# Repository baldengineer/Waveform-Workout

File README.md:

# Waveform-Workout

An open-source tool to test oscilloscopes for basic operation.

## Status

r1 is at the fab.

## Firmware

[Build and flash the trainer](firmware/README.md). The first boot starts both outputs with a 1 kHz sine at 1.00 Vpp centered on +0.75 V. Later boots restore the last selection from EEPROM. Use MODE and VALUE or the USB shell to select waveform, DC, XY and trigger exercises. An optional SSD1306 OLED on J6 shows the active mode and value.

## Design files

- [Schematic PDF](kicad/Waveform%20Workout%20Schematic.pdf)
- [PCB PDF](kicad/Waveform%20Workout%20PCB.pdf)
- [Open the project in KiCanvas](https://kicanvas.org/?repo=https%3A%2F%2Fgithub.com%2Fbaldengineer%2FWaveform-Workout%2Ftree%2Fmain%2Fkicad)

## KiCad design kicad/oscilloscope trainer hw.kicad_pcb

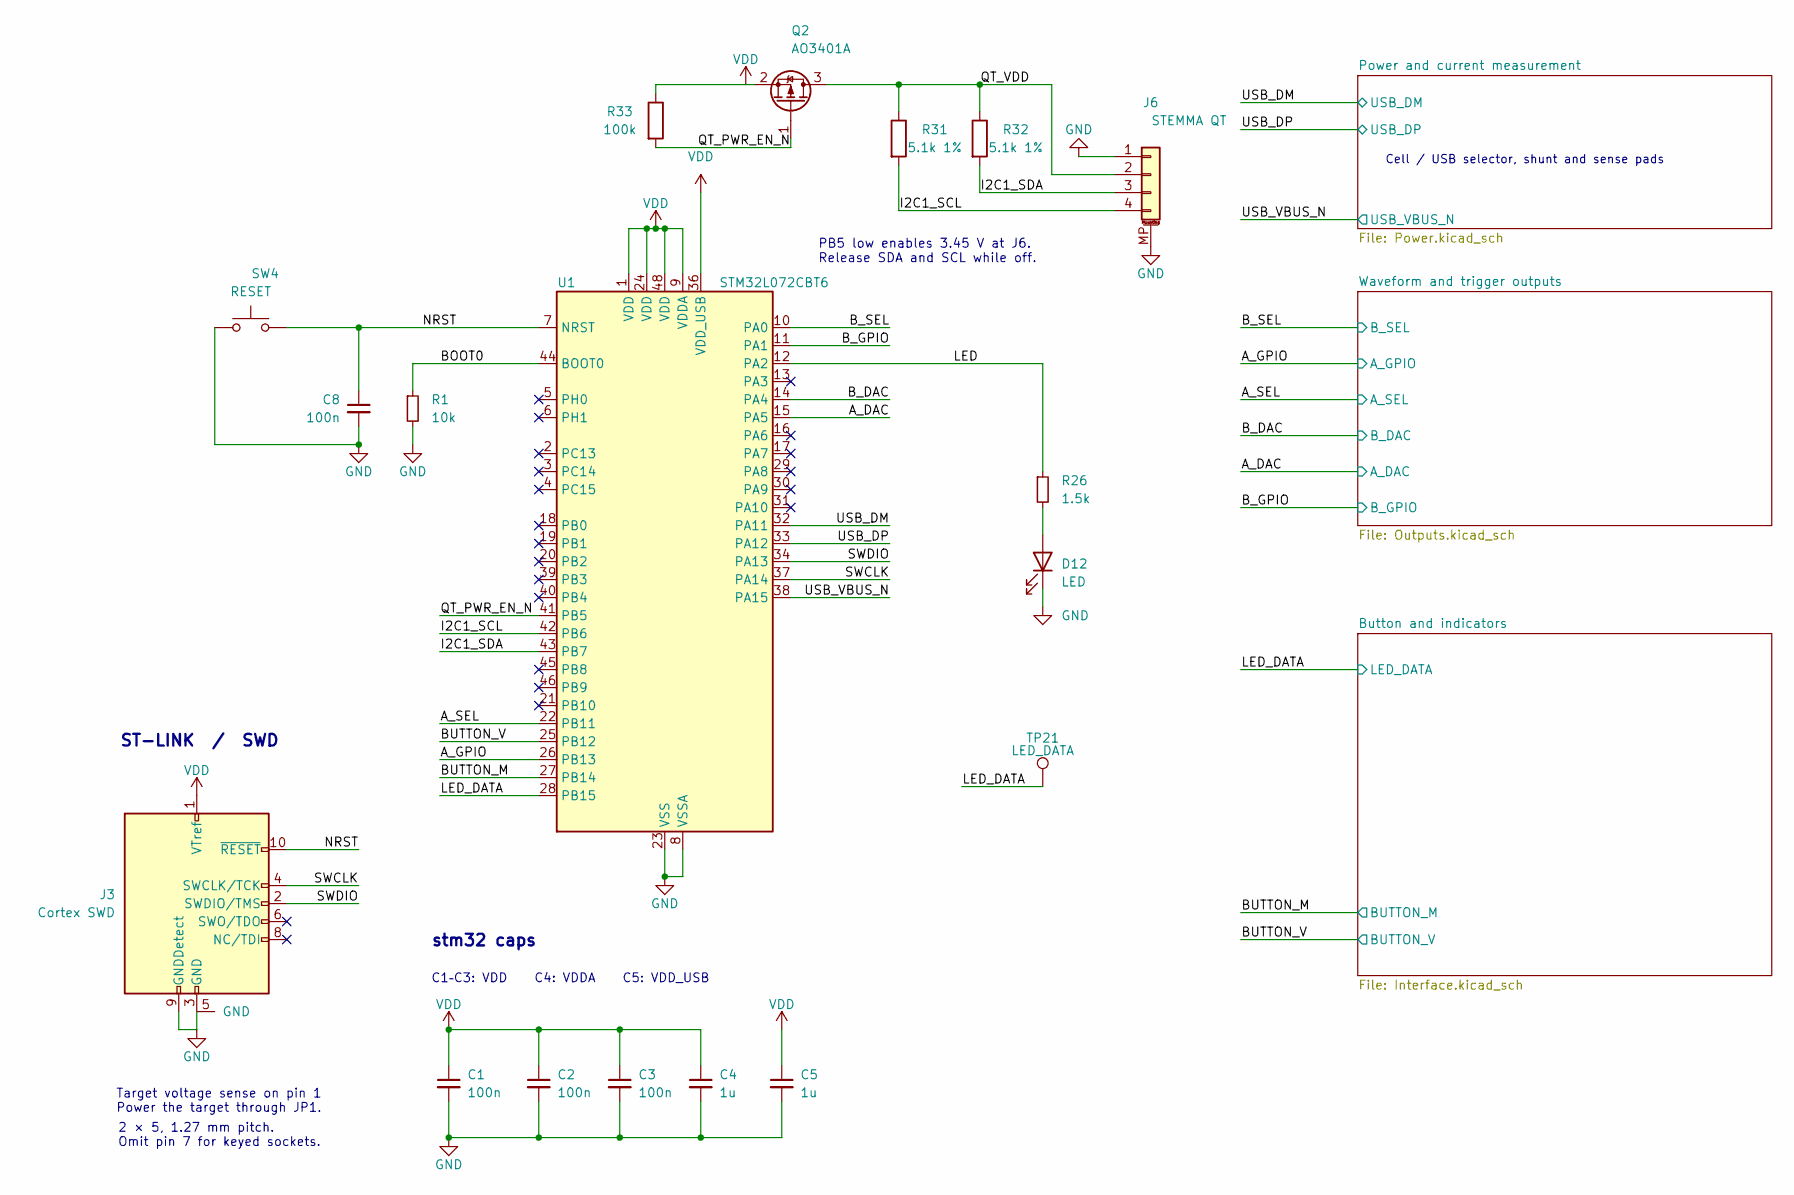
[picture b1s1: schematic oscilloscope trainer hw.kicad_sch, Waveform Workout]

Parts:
C1, C2, C3, C8: 100n; C_0603_1608Metric; MPN CC0603KRX7R9BB104; LCSC C14663
C4, C5: 1u; C_0603_1608Metric; MPN CC0603KRX5R9BB105; LCSC C128624
D12: LED; LED_0805_2012Metric; MPN KT-0805G; LCSC C2297
J3: Cortex SWD; Samtec_FTSH-105-01-L-DV-007-TR; MPN FTSH-105-01-L-DV-007-TR; LCSC C3347749
J6: STEMMA QT; JST_SH_SM04B-SRSS-TB_1x04-1MP_P1.00mm_Horizontal; MPN SM04B-SRSS-TB(LF)(SN); LCSC C160404
Q2: AO3401A; SOT-23; MPN AO3401A; LCSC C15127
R1: 10k; R_0603_1608Metric; MPN RC0603FR-0710KL; LCSC C98220
R26: 1.5k; R_0603_1608Metric; MPN 0603WAF1501T5E; LCSC C22843
R31, R32: 5.1k 1%; R_0603_1608Metric; MPN 0603WAF5101T5E; LCSC C23186
R33: 100k; R_0603_1608Metric; MPN 0603WAF1003T5E; LCSC C25803
SW4: RESET; SW_SPST_TS-1088-xR020; MPN TS-1088-AR02016; LCSC C720477
TP21: PB15; Harwin-S1751-46-Test-Point; MPN S1751-46; LCSC C3029083
U1: STM32L072CBT6; LQFP-48_7x7mm_P0.5mm; MPN STM32L072CBT6; LCSC C465977

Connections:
/A_DAC: U1.15 (PA5); also elsewhere on the board
/A_GPIO: U1.26 (PB13); also elsewhere on the board
/A_SEL: U1.22 (PB11); also elsewhere on the board
/BOOT0: R1.1, U1.44 (BOOT0)
/BUTTON_M: U1.27 (PB14); also elsewhere on the board
/BUTTON_V: U1.25 (PB12); also elsewhere on the board
/B_DAC: U1.14 (PA4); also elsewhere on the board
/B_GPIO: U1.11 (PA1); also elsewhere on the board
/B_SEL: U1.10 (PA0); also elsewhere on the board
/I2C1_SCL: J6.4, R31.2, U1.42 (PB6)
/I2C1_SDA: J6.3, R32.2, U1.43 (PB7)
/LED: R26.1, U1.12 (PA2)
/LED_DATA: TP21.1 (1_1), U1.28 (PB15); also elsewhere on the board
/NRST: C8.1, J3.10 (~RESET), SW4.2, U1.7 (NRST)
/QT_PWR_EN_N: Q2.1 (G), R33.2, U1.41 (PB5)
/QT_VDD: J6.2, Q2.3 (D), R31.1, R32.1
/SWCLK: J3.4 (SWCLK/TCK), U1.37 (PA14)
/SWDIO: J3.2 (SWDIO/TMS), U1.34 (PA13)
/USB_DM: U1.32 (PA11); also elsewhere on the board
/USB_DP: U1.33 (PA12); also elsewhere on the board
/USB_VBUS_N: U1.38 (PA15); also elsewhere on the board
unnamed: D12.2 (A), R26.2
VDD: C1.1, C2.1, C3.1, C4.1, C5.1, J3.1 (VTref), Q2.2 (S), R33.1, U1.1 (VDD), U1.9 (VDDA), U1.24 (VDD), U1.36 (VDD_USB), U1.48 (VDD); also elsewhere on the board

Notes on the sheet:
C1–C3: VDD C4: VDDA C5: VDD_USB
Target voltage sense on pin 1 Power the target through JP1.
PB5 low enables 3.45 V at J6. Release SDA and SCL while off.
ST-LINK / SWD
Cell / USB selector, shunt and sense pads
stm32 caps
2 × 5, 1.27 mm pitch. Omit pin 7 for keyed sockets.

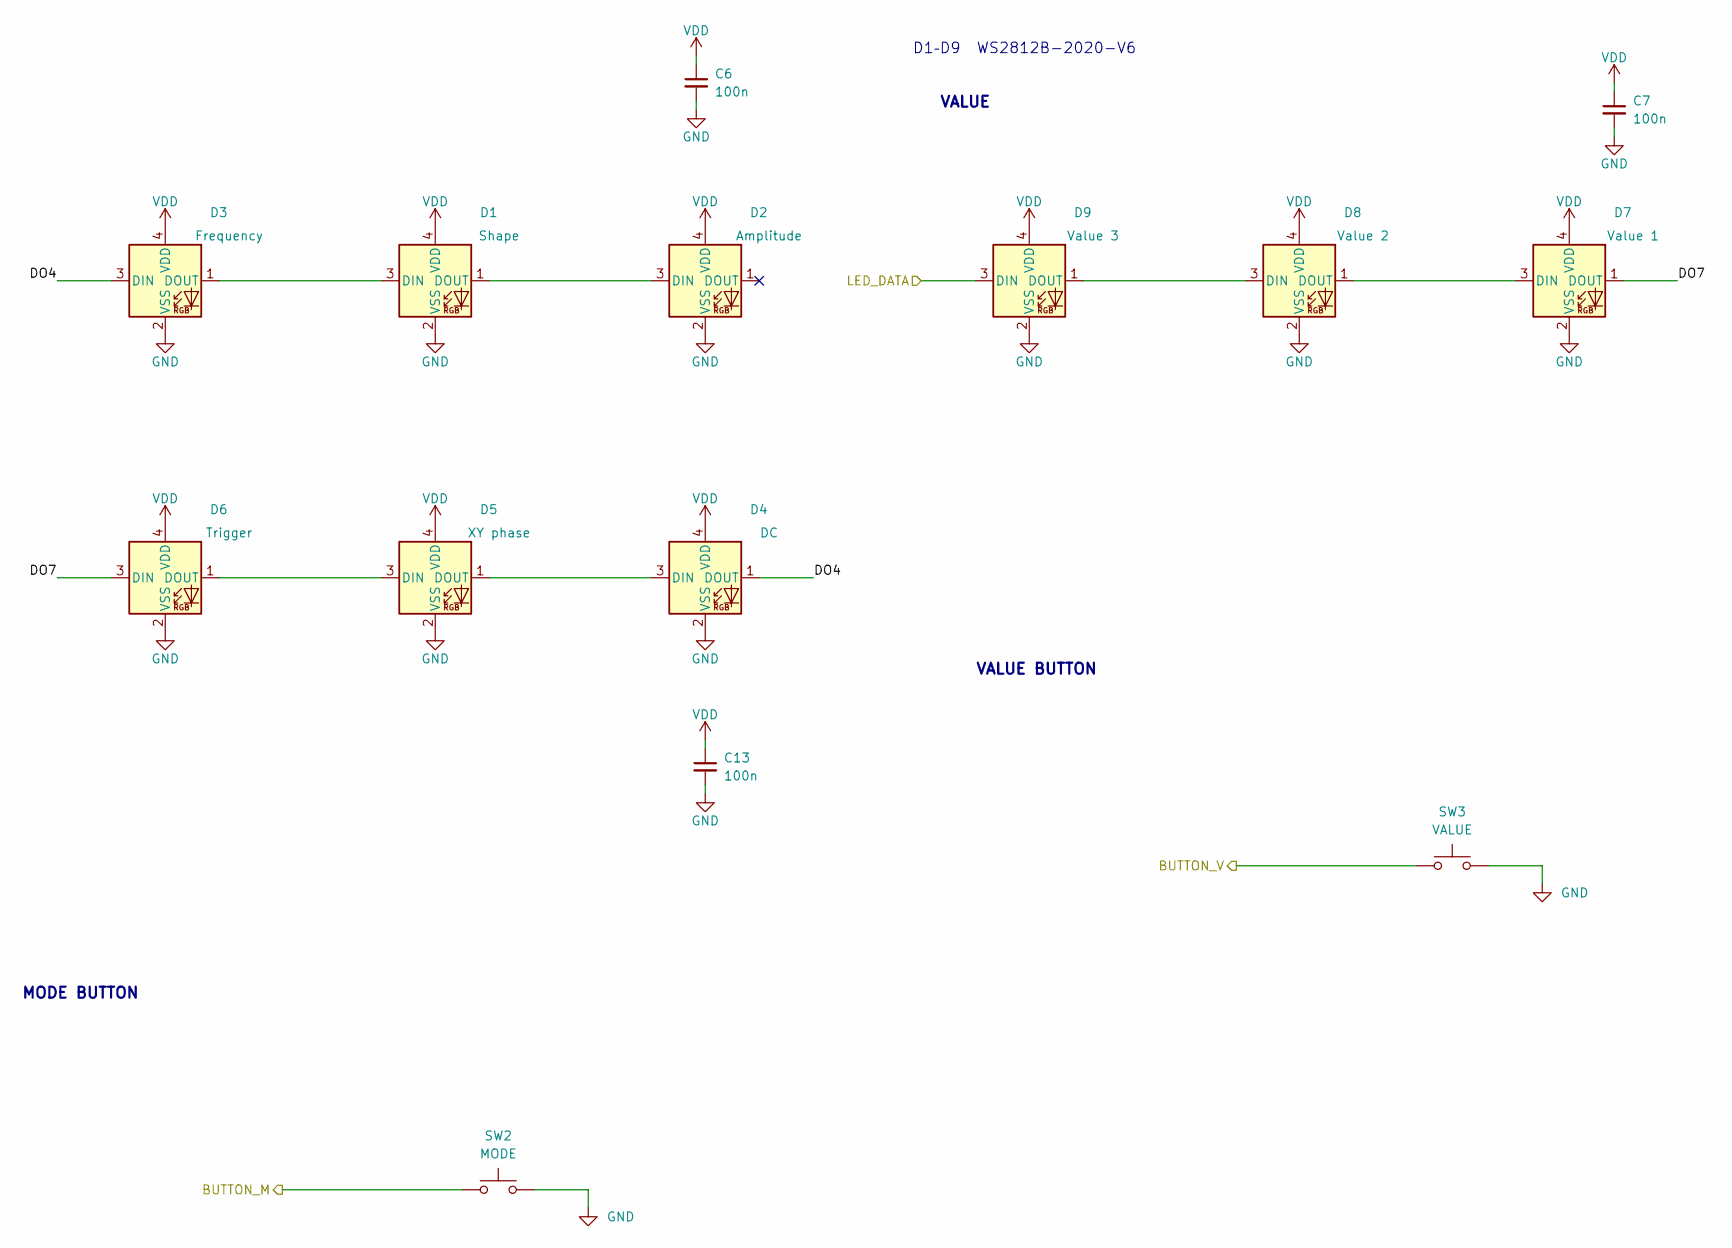
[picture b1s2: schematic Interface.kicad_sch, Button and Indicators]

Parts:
C6, C7, C13: 100n; C_0603_1608Metric; MPN CC0603KRX7R9BB104; LCSC C14663
D1, D2, D3, D4, D5, D6, D7, D8, D9: WS2812B-2020-V6; LED_WS2812B-2020_PLCC4_2.0x2.0mm; MPN WS2812B-2020-V6; LCSC C52917434
SW2: MODE; SW_SPST_TS-1088-xR020; MPN TS-1088-AR02016; LCSC C720477
SW3: VALUE; SW_SPST_TS-1088-xR020; MPN TS-1088-AR02016; LCSC C720477

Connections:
/BUTTON_M: SW2.1; also elsewhere on the board
/BUTTON_V: SW3.1; also elsewhere on the board
/Button and indicators/DO4: D3.3 (DIN), D4.1 (DOUT)
/Button and indicators/DO7: D6.3 (DIN), D7.1 (DOUT)
/LED_DATA: D9.3 (DIN); also elsewhere on the board
unnamed: D1.3 (DIN), D3.1 (DOUT)
unnamed: D1.1 (DOUT), D2.3 (DIN)
unnamed: D4.3 (DIN), D5.1 (DOUT)
unnamed: D5.3 (DIN), D6.1 (DOUT)
unnamed: D7.3 (DIN), D8.1 (DOUT)
unnamed: D8.3 (DIN), D9.1 (DOUT)
VDD: C6.1, C7.1, C13.1, D1.4 (VDD), D2.4 (VDD), D3.4 (VDD), D4.4 (VDD), D5.4 (VDD), D6.4 (VDD), D7.4 (VDD), D8.4 (VDD), D9.4 (VDD); also elsewhere on the board

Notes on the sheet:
VALUE
MODE BUTTON
VALUE BUTTON
D1–D9 WS2812B-2020-V6

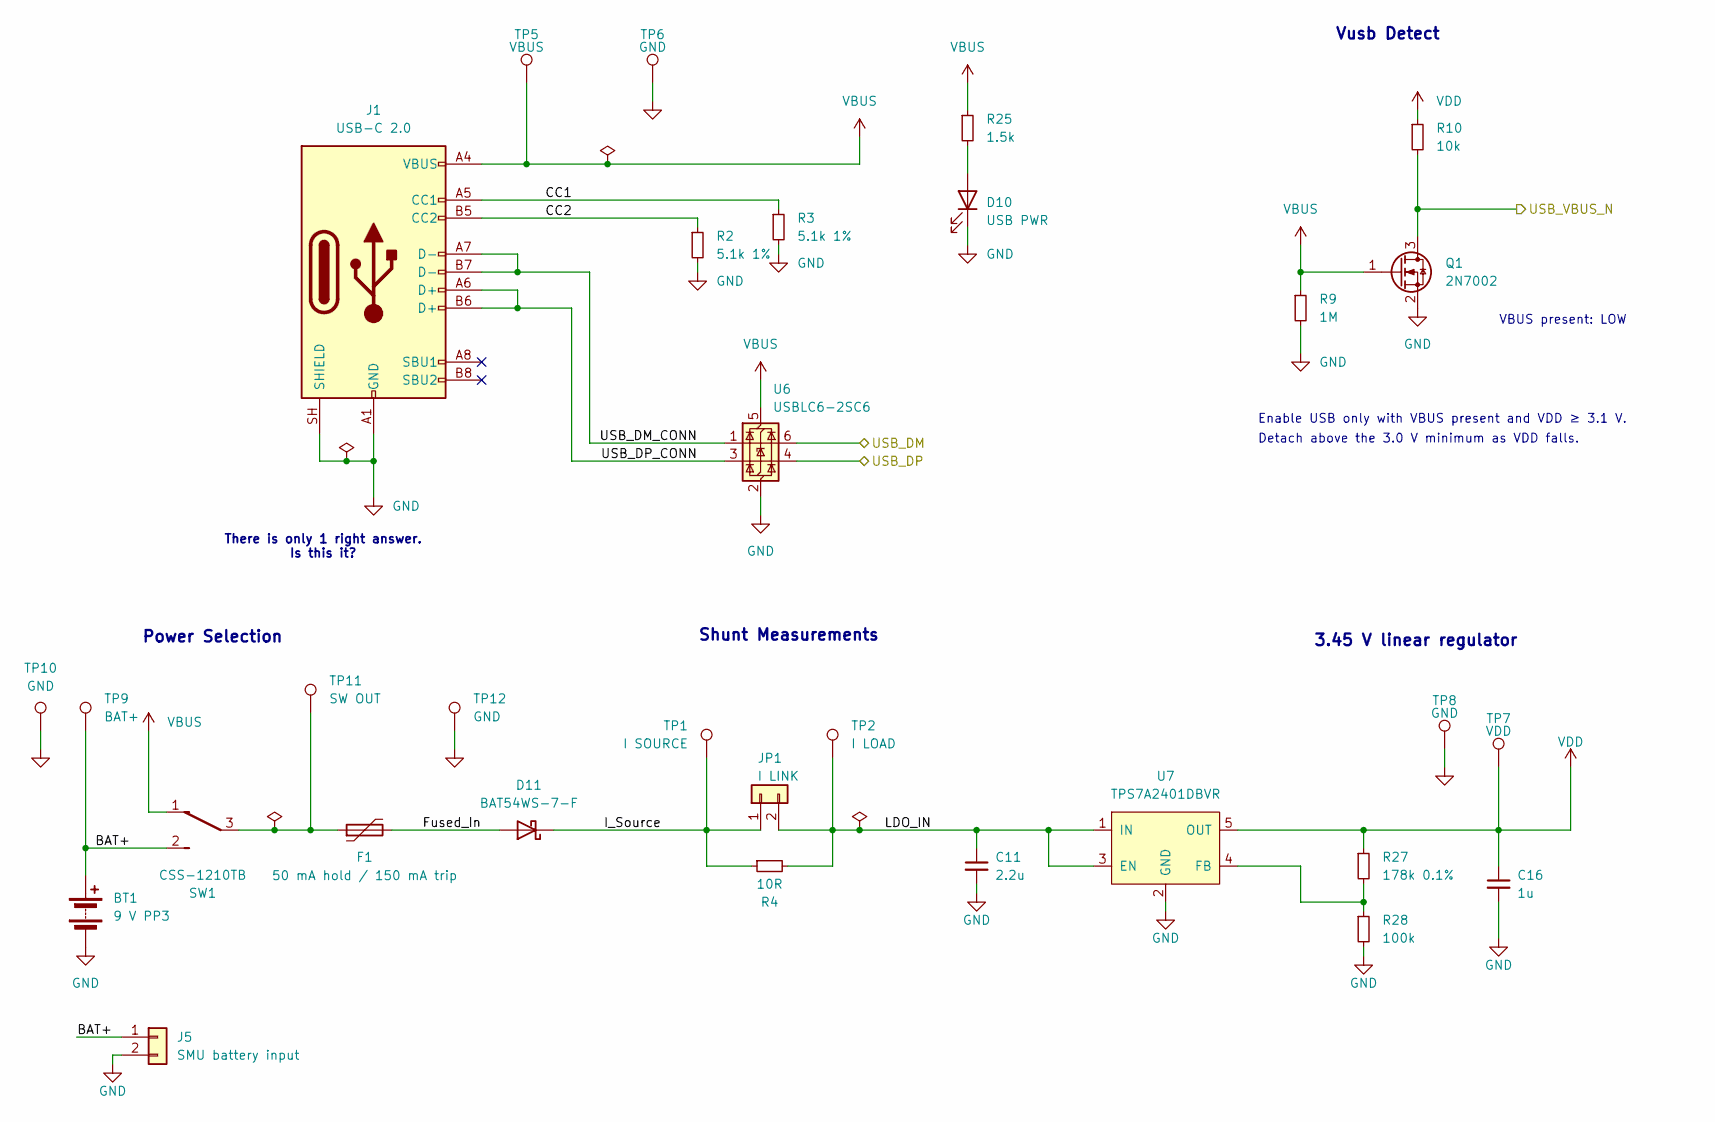
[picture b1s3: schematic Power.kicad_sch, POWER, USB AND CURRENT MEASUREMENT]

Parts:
BT1: 9 V PP3; BatteryHolder_Keystone_1290-79_1xPP3_Adhesive_Wire; MPN 1290-79
C11: 2.2u; C_0603_1608Metric; MPN CL10A225KO8NNNC; LCSC C23630
C16: 1u; C_0603_1608Metric; MPN CC0603KRX5R9BB105; LCSC C128624
D10: USB PWR; LED_0805_2012Metric; MPN KT-0805G; LCSC C2297
D11: BAT54WS-7-F; D_SOD-323; MPN BAT54WS-7-F; LCSC C124205
F1: 50 mA hold / 150 mA trip; Fuse_1206_3216Metric; MPN 1206L005/60WR; LCSC C315892
J1: USB-C 2.0; USB_C_Receptacle_GCT_USB4105-xx-A_16P_TopMnt_Horizontal; MPN USB4105-GF-A; LCSC C3020560
J5: SMU battery input; PinHeader_1x02_P2.54mm_Vertical; MPN PZ254V-11-02P; LCSC C492401
JP1: I LINK; PinHeader_1x02_P2.54mm_Vertical; MPN PZ254V-11-02P; LCSC C492401
Q1: 2N7002; SOT-23; MPN 2N7002; LCSC C8545
R2, R3: 5.1k 1%; R_0603_1608Metric; MPN 0603WAF5101T5E; LCSC C23186
R4: 10R; R_0805_2012Metric; MPN 0805W8F100JT5E; LCSC C17415
R9: 1M; R_0603_1608Metric; MPN 0603WAF1004T5E; LCSC C22935
R10: 10k; R_0603_1608Metric; MPN RC0603FR-0710KL; LCSC C98220
R25: 1.5k; R_0603_1608Metric; MPN 0603WAF1501T5E; LCSC C22843
R27: 178k 0.1%; R_0603_1608Metric; MPN ARG03BTC1783; LCSC C2441185
R28: 100k; R_0603_1608Metric; MPN 0603WAF1003T5E; LCSC C25803
SW1: CSS-1210TB; SW_SPDT_Nidec_CSS-1210TB; MPN CSS-1210TB; LCSC C2921710
TP1: I SOURCE; Harwin-S1751-46-Test-Point; MPN S1751-46; LCSC C3029083
TP2: I LOAD; Harwin-S1751-46-Test-Point; MPN S1751-46; LCSC C3029083
TP5: VBUS; Harwin-S1751-46-Test-Point; MPN S1751-46; LCSC C3029083
TP6, TP8, TP10, TP12: GND; Harwin-S1751-46-Test-Point; MPN S1751-46; LCSC C3029083
TP7: VDD; Harwin-S1751-46-Test-Point; MPN S1751-46; LCSC C3029083
TP9: BAT+; Harwin-S1751-46-Test-Point; MPN S1751-46; LCSC C3029083
TP11: SW OUT; Harwin-S1751-46-Test-Point; MPN S1751-46; LCSC C3029083
U6: USBLC6-2SC6; SOT-23-6; MPN USBLC6-2SC6; LCSC C7519
U7: TPS7A2401DBVR; SOT-23-5; MPN TPS7A2401DBVR; LCSC C2693328

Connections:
/Power and current measurement/BAT+: BT1.1 (+), J5.1, SW1.2 (B), TP9.1 (1_1)
/Power and current measurement/CC1: J1.A5 (CC1), R3.1
/Power and current measurement/CC2: J1.B5 (CC2), R2.1
/Power and current measurement/Fused_In: D11.2 (A), F1.2
/Power and current measurement/I_Source: D11.1 (K), JP1.1, R4.1, TP1.1 (1_1)
/Power and current measurement/USB_DM_CONN: J1.A7 (D-), J1.B7 (D-), U6.1 (I/O1)
/Power and current measurement/USB_DP_CONN: J1.A6 (D+), J1.B6 (D+), U6.3 (I/O2)
/USB_DM: U6.6 (I/O1); also elsewhere on the board
/USB_DP: U6.4 (I/O2); also elsewhere on the board
/USB_VBUS_N: Q1.3 (D), R10.2; also elsewhere on the board
unnamed: D10.2 (A), R25.2
unnamed: R27.2, R28.1, U7.4 (FB)
VDD: C16.1, R10.1, R27.1, TP7.1 (1_1), U7.5 (OUT); also elsewhere on the board

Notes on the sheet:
Shunt Measurements
3.45 V linear regulator
Vusb Detect
Enable USB only with VBUS present and VDD ≥ 3.1 V.
Power Selection
VBUS present: LOW
There is only 1 right answer. Is this it?
Detach above the 3.0 V minimum as VDD falls.

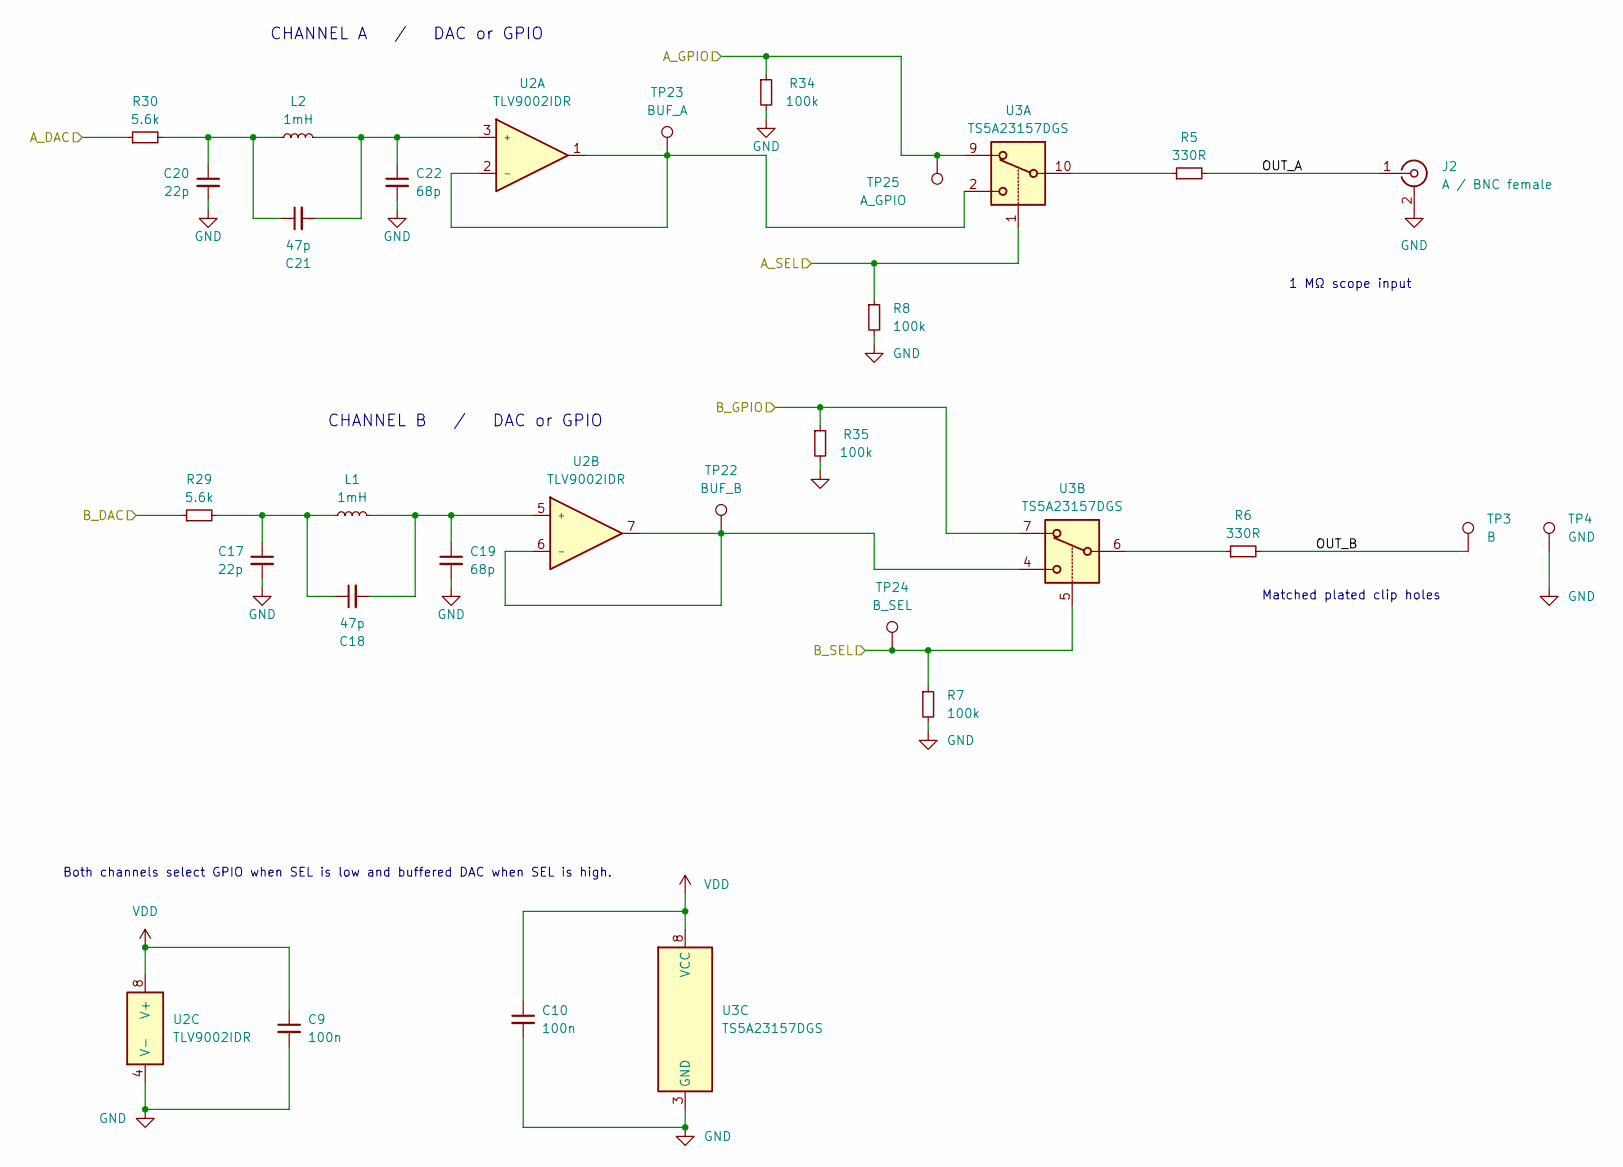
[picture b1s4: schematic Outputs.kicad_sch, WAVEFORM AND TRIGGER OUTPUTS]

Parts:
C9, C10: 100n; C_0603_1608Metric; MPN CC0603KRX7R9BB104; LCSC C14663
C17, C20: 22p; C_0805_2012Metric_Pad1.18x1.45mm_HandSolder; MPN CL21C220JBANNNC; LCSC C1804
C18, C21: 47p; C_0805_2012Metric_Pad1.18x1.45mm_HandSolder; MPN CL21C470JBANNNC; LCSC C14857
C19, C22: 68p; C_0805_2012Metric_Pad1.18x1.45mm_HandSolder; MPN 0805CG680J500NT; LCSC C1834
J2: A / BNC female; BNC_Kinghelm_KH-BNC50-3511_Horizontal; MPN KH-BNC50-3511; LCSC C2837587
L1, L2: 1mH; L_1812_4532Metric_Pad1.30x3.40mm_HandSolder; MPN 1812LS-105XJRC
R5, R6: 330R; R_0603_1608Metric; MPN 0603WAF3300T5E; LCSC C23138
R7, R8, R34, R35: 100k; R_0603_1608Metric; MPN 0603WAF1003T5E; LCSC C25803
R29, R30: 5.6k; R_0805_2012Metric_Pad1.20x1.40mm_HandSolder; MPN 0805W8F5601T5E; LCSC C4382
TP3: B; TestPoint_Plated_Hole_D3.0mm
TP4: GND; Harwin-S1751-46-Test-Point; MPN S1751-46; LCSC C3029083
TP22: BUF_B; Harwin-S1751-46-Test-Point; MPN S1751-46; LCSC C3029083
TP23: BUF_A; Harwin-S1751-46-Test-Point; MPN S1751-46; LCSC C3029083
TP24: B_SEL; Harwin-S1751-46-Test-Point; MPN S1751-46; LCSC C3029083
TP25: A_GPIO; Harwin-S1751-46-Test-Point; MPN S1751-46; LCSC C3029083
U2: TLV9002IDR; SOIC-8_3.9x4.9mm_P1.27mm; MPN TLV9002IDR; LCSC C398360
U3: TS5A23157DGS; TSSOP-10_3x3mm_P0.5mm; MPN TS5A23157DGSR; LCSC C11133

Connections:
/A_DAC: R30.1; also elsewhere on the board
/A_GPIO: R34.1, TP25.1 (1_1), U3.9; also elsewhere on the board
/A_SEL: R8.1, U3.1; also elsewhere on the board
/B_DAC: R29.1; also elsewhere on the board
/B_GPIO: R35.1, U3.7; also elsewhere on the board
/B_SEL: R7.1, TP24.1 (1_1), U3.5; also elsewhere on the board
/Waveform and trigger outputs/OUT_A: J2.1 (In), R5.2
/Waveform and trigger outputs/OUT_B: R6.2, TP3.1 (1_1)
unnamed: C17.1, C18.1, L1.1, R29.2
unnamed: C20.1, C21.1, L2.1, R30.2
unnamed: R5.1, U3.10
unnamed: R6.1, U3.6
unnamed: C21.2, C22.1, L2.2, U2.3 (+)
unnamed: TP23.1 (1_1), U2.1, U2.2 (−), U3.2
unnamed: C18.2, C19.1, L1.2, U2.5 (+)
unnamed: TP22.1 (1_1), U2.6 (−), U2.7, U3.4
VDD: C9.1, C10.1, U2.8 (V+), U3.8 (VCC); also elsewhere on the board

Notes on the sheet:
Matched plated clip holes
Both channels select GPIO when SEL is low and buffered DAC when SEL is high.
CHANNEL B / DAC or GPIO
1 MΩ scope input
CHANNEL A / DAC or GPIO

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
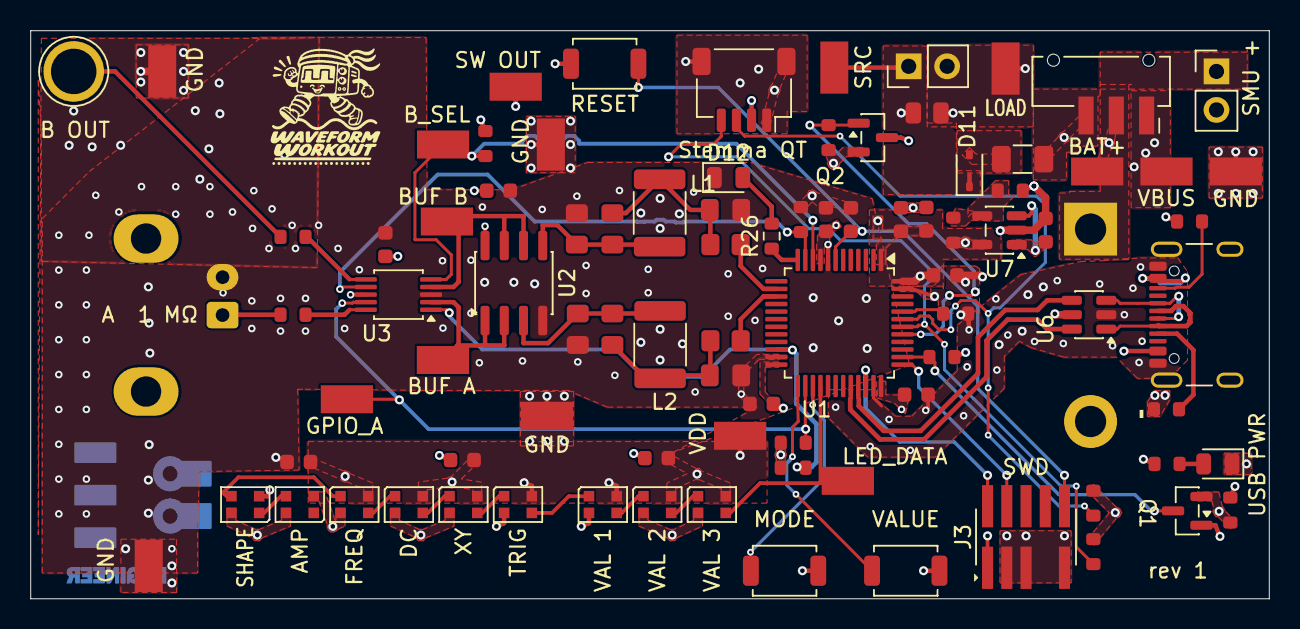
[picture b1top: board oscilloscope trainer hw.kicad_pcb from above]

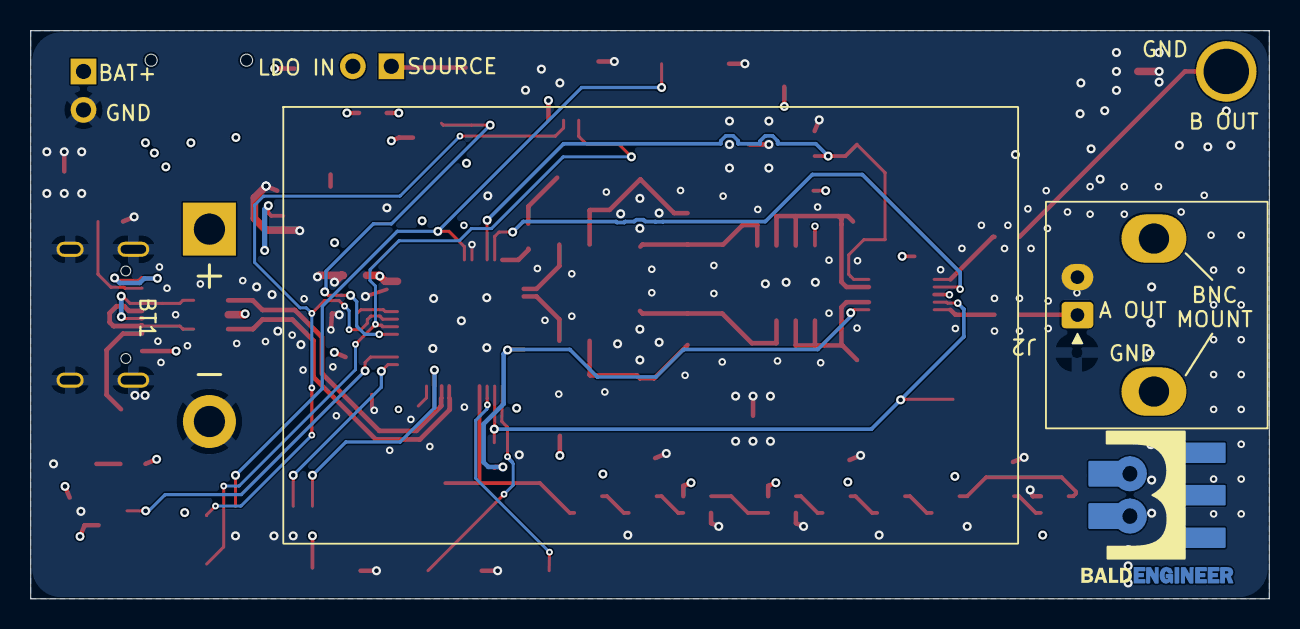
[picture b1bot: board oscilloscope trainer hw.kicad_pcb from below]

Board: 4 copper layers, 81.8 x 37.5 mm, 91 parts (3 on the bottom side), 54 nets.

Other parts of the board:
svg2mod: G***; BE10v2

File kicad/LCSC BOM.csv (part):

References,Fit qty per trainer,Part / schematic value,Manufacturer,MPN,LCSC,Ready to ship at check,Checked UTC,LCSC product page,Assembly / sourcing status,Footprint,Notes,Datasheet
BT1,1,9 V PP3,Keystone Electronics,1290-79,,,,,External sourcing,Trainer:BatteryHolder_Keystone_1290-79_1xPP3_Adhesive_Wire,Glue the holder to the back with electrically insulating adhesive. Wire the positive lug to pad 1 (BAT+) and the negative lug to pad 2 (GND). Remove the PP3 before applying an external battery-emulation voltage to J5.,https://media.soselectronic.com/KatList/keystone/1290-79.pdf
BT1 battery,1,9 V alkaline PP3,,,,,,,User supplied,,Remove the battery when using J5 for SMU emulation.,
"C1, C2, C3, C6, C7, C8, C9, C10, C13",9,100n,YAGEO,CC0603KRX7R9BB104,C14663,908800,2026-11-23T04:45:07Z,https://www.lcsc.com/product-detail/C14663.html,Populate,Capacitor_SMD:C_0603_1608Metric,,https://datasheet.lcsc.com/datasheet/pdf/23ccee80ee542e7cf15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
"C4, C5, C16",3,1u,YAGEO,CC0603KRX5R9BB105,C128624,135600,2026-11-23T04:45:06Z,https://www.lcsc.com/product-detail/C128624.html,Populate,Capacitor_SMD:C_0603_1608Metric,"1 µF, 50 V, X5R, ±10%.",https://datasheet.lcsc.com/datasheet/pdf/5b3aae1e7925073bc9b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
C11,1,2.2u,Samsung Electro-Mechanics,CL10A225KO8NNNC,C23630,288150,2026-11-23T04:45:09Z,https://www.lcsc.com/product-detail/C23630.html,Populate,Capacitor_SMD:C_0603_1608Metric,,https://datasheet.lcsc.com/datasheet/pdf/02336ea48ea44ca18c7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
"C17, C20",2,22p,Samsung Electro-Mechanics,CL21C220JBANNNC,C1804,132200,2026-11-23T04:45:08Z,https://www.lcsc.com/product-detail/C1804.html,Populate,Capacitor_SMD:C_0805_2012Metric_Pad1.18x1.45mm_HandSolder,"DAC filter, 0805 C0G, 50 V, ±5%.",https://datasheet.lcsc.com/datasheet/pdf/02336ea48ea44ca18c7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
"C18, C21",2,47p,Samsung Electro-Mechanics,CL21C470JBANNNC,C14857,82360,2026-11-23T04:45:07Z,https://www.lcsc.com/product-detail/C14857.html,Populate,Capacitor_SMD:C_0805_2012Metric_Pad1.18x1.45mm_HandSolder,"DAC filter tank capacitors, 0805 C0G, 50 V, ±5%.",https://datasheet.lcsc.com/datasheet/pdf/02336ea48ea44ca18c7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
"C19, C22",2,68p,FH,0805CG680J500NT,C1834,28200,2026-11-23T04:45:08Z,https://www.lcsc.com/product-detail/C1834.html,Populate,Capacitor_SMD:C_0805_2012Metric_Pad1.18x1.45mm_HandSolder,"DAC filter, 0805 C0G, 50 V, ±5%.",https://datasheet.lcsc.com/datasheet/pdf/09fe2daf22580a99fa7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
"D1, D2, D3, D4, D5, D6, D7, D8, D9",9,WS2812B-2020-V6,Worldsemi,WS2812B-2020-V6,C52917434,688000,2026-11-23T04:45:12Z,https://www.lcsc.com/product-detail/C52917434.html,Populate,Trainer:LED_WS2812B-2020_PLCC4_2.0x2.0mm,"Six mode and three value indicators. Data from PB15 passes through D9, D8, D7, D6, D5, D4, D3, D1, then D2. Limit brightness and simultaneous channel current in firmware.",https://www.world-semi.com/downloads/datasheets/en/ws2812b-2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
D10,1,"USB power indicator, green 0805",Hubei KENTO Electronics,KT-0805G,C2297,2056300,2026-11-23T04:45:09Z,https://www.lcsc.com/product-detail/C2297.html,Populate,LED_SMD:LED_0805_2012Metric,Independent USB power indication with R25.,https://datasheet.lcsc.com/datasheet/pdf/de342fde3322df07970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
D11,1,BAT54WS-7-F,Diodes Incorporated,BAT54WS-7-F,C124205,79715,2026-11-23T04:45:06Z,https://www.lcsc.com/product-detail/C124205.html,Populate,Diode_SMD:D_SOD-323,Anode (pad 2) connects to F1. Cathode (pad 1) feeds the source side of JP1 and R4 at TP1.,https://www.diodes.com/datasheet/download/BAT54WS.pdf
F1,1,50 mA hold / 150 mA trip,Littelfuse,1206L005/60WR,C315892,,,https://www.lcsc.com/product-detail/C315892.html,Populate,Fuse:Fuse_1206_3216Metric,"60 V surface-mount resettable PPTC for the trainer and accessory supply. Maximum time to trip is 1.5 s at 250 mA.",https://www.littelfuse.com/assetdocs/littelfuse-ptc-1206l-da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
J1,1,USB-C 2.0,GCT,USB4105-GF-A,C3020560,749,2026-11-23T04:45:11Z,https://www.lcsc.com/product-detail/C3020560.html,Populate,Connector_USB:USB_C_Receptacle_GCT_USB4105-xx-A_16P_TopMnt_Horizontal,,https://gct.co/files/drawings/usb4105.pdf
J2,1,A / BNC female,Kinghelm,KH-BNC50-3511,C2837587,9313,2026-11-23T04:45:10Z,https://www.lcsc.com/product-detail/C2837587.html,Populate,Trainer:BNC_Kinghelm_KH-BNC50-3511_Horizontal,50 ohm right-angle through-hole jack with panel nut and washer. Use a male-to-male BNC coupler with the scope's 1 megohm input.,https://www.kinghelm.com.cn/upload/file/20221214/KH-BNC50-3511.pdf
J3,1,Cortex SWD,Samtec,FTSH-105-01-L-DV-007-TR,C3347749,,,https://www.lcsc.com/product-detail/C3347749.html,Populate,Trainer:Samtec_FTSH-105-01-L-DV-007-TR,"Vertical 1.27 mm SMT Cortex debug header, position 7 omitted.",https://suddendocs.samtec.com/prints/ftsh-1xx-xx-xxx-dv-xxx-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
J5,1,SMU battery input,XFCN,PZ254V-11-02P,C492401,883050,2026-11-23T04:45:12Z,https://www.lcsc.com/product-detail/C492401.html,Populate,Connector_PinHeader_2.54mm:PinHeader_1x02_P2.54mm_Vertical,Vertical 2.54 mm two-pin header. Connect SMU Force HI to pin 1 (BAT+) and Force LO to pin 2 (GND). Leave BT1 empty during battery emulation.,https://datasheet.lcsc.com/datasheet/pdf/3b85a1cdf6ed945f2e2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
J6,1,STEMMA QT,JST,SM04B-SRSS-TB(LF)(SN),C160404,,,https://www.lcsc.com/product-detail/C160404.html,Populate,Connector_JST:JST_SH_SM04B-SRSS-TB_1x04-1MP_P1.00mm_Horizontal,"Side-entry JST SH, 1.0 mm pitch. Pin 1 GND, 2 switched 3.45 V, 3 SDA (PB7), 4 SCL (PB6). Accessory power output; do not drive from another supply.",https://www.jst-mfg.com/product/pdf/eng/eSH.pdf
JP1,1,I LINK,XFCN,PZ254V-11-02P,C492401,883050,2026-11-23T04:45:12Z,https://www.lcsc.com/product-detail/C492401.html,Populate,Connector_PinHeader_2.54mm:PinHeader_1x02_P2.54mm_Vertical,"Fit the shorting cap for normal operation. To measure U7 input current, remove the cap and connect an ammeter across JP1 with R4 unpopulated. The USB indicator D10 draws directly from VBUS.",https://datasheet.lcsc.com/datasheet/pdf/3b85a1cdf6ed945f2e2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
JP1 cap,1,2.54 mm shorting cap,BOOMELE,2.54,C100114,378100,2026-11-23T04:45:05Z,https://www.lcsc.com/product-detail/C100114.html,Fit on header,,Install on JP1 for normal operation.,
"L1, L2",2,1mH,Coilcraft,1812LS-105XJLC,C22416512,10,2026-11-23T05:04:37Z,https://www.lcsc.com/product-detail/C22416512.html,Populate,Inductor_SMD:L_1812_4532Metric_Pad1.30x3.40mm_HandSolder,"Purchasing alternative to schematic 1812LS-105XJRC. Same winding and package with Ag-Pd-Pt terminations. Lower-cost bench candidate: Bourns PM1812-102J-RC (https://www.lcsc.com/product-detail/C913278.html), 26 ready to ship at this check. Verify 250 kHz gain and 750 kHz notch frequency and depth before substituting the Bourns part.",https://www.coilcraft.com/getmedia/1df56443-b7c7-4f17-abaf-4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
Q1,1,2N7002,Jiangsu Changjing Electronics Technology,2N7002,C8545,5426900,2026-11-23T04:45:13Z,https://www.lcsc.com/product-detail/C8545.html,Populate,Package_TO_SOT_SMD:SOT-23,,https://datasheet.lcsc.com/datasheet/pdf/a141b8bd86b14475955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
Q2,1,AO3401A,Alpha & Omega Semiconductor,AO3401A,C15127,,,https://www.lcsc.com/product-detail/C15127.html,Populate,Package_TO_SOT_SMD:SOT-23,"P-channel high-side switch. Pin 1 gate (PB5, active low), 2 source (measured VDD), 3 drain (QT_VDD). R33 defaults the port off.",https://www.aosmd.com/sites/default/files/res/datasheets/AO3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
"R1, R10",2,10k,YAGEO,RC0603FR-0710KL,C98220,5240700,2026-11-23T04:46:02Z,https://www.lcsc.com/product-detail/C98220.html,Populate,Resistor_SMD:R_0603_1608Metric,,https://datasheet.lcsc.com/datasheet/pdf/b426be3ce22c6de3e0c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
"R2, R3, R31, R32",4,5.1k 1%,UNI-ROYAL,0603WAF5101T5E,C23186,12810600,2026-11-23T04:45:09Z,https://www.lcsc.com/product-detail/C23186.html,Populate,Resistor_SMD:R_0603_1608Metric,R2 and R3 terminate USB CC. R31 and R32 pull SCL and SDA up to switched QT_VDD.,https://datasheet.lcsc.com/datasheet/pdf/0a975aaa49b7c97f38a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
